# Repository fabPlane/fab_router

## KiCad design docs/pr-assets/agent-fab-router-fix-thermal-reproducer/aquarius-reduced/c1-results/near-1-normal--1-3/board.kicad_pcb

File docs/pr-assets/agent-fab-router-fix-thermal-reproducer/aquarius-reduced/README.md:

# Rotated back-layer thermal failure reduced from the completed baseline

This static native reproducer preserves Aquarius U1.39 (315-degree rounded
rectangle, 75 micrometre corner radius) and its B.Cu zone. It has one pad,
three 0.2032 mm tracks, no vias, and one zone. Its sole native error is
`starved_thermal`: one spoke, minimum two. This is not a router fix or a new
routing benchmark. All 27 baseline thermal errors remain unresolved.

Fresh native refill plus DRC, same host and cores 20–25, three repeats per row:

| Fixture control | Before: all tracks | After: indicated deletion |
| --- | ---: | ---: |
| First track removed | 1 error, 0 opens each | 0 errors, 0 opens each |
| Second track removed | 1 error, 0 opens each | 0 errors, 0 opens each |
| Third track removed | 1 error, 0 opens each | 0 errors, 0 opens each |
| All tracks removed | 1 error, 0 opens each | 0 errors, 0 opens each |

The shared before column describes the same three runs, not twelve runs.
Fifteen native checks total. Deleting obstacles is a diagnostic control and
would discard intended routing; it is not an acceptable production remedy.
The three non-ground tracks have different nets. Their terminals have been
removed, so zero opens in this static fixture does not establish completion
of those nets. There is no routing attempt, engine regression, or native
transaction implementation here.

The reducer first retained objects whose native bounding boxes intersect a
2 mm square radius around the pad, then deleted pad/copper/zone UUID groups
while requiring the exact target and no other error. Single-object deletion
trials finish the search. This establishes irreducibility only among retained
candidate objects; the board outline, zone polygon, graphics and unused net
definitions have not been geometrically minimized. `reduction.json` retains
24 trials and their exact native findings.

`provenance.json` verifies that pad geometry, each retained track and the full
zone definition (excluding refill polygons) match the completed baseline
output. Both project and rule sidecars match the output and original input
byte-for-byte. The pad position is the baseline output position, with its
previously recorded +8/-46 nm displacement from the original input. That
small displacement is not attributed to the failure. `LICENSE` preserves
the source board license.

`board.dsn` is a native export for further engine diagnostics. It does not
encode native thermal metadata and is not claimed to reproduce native
starvation when routed independently. Keep the native board and sidecars.
`results/` retains all fifteen refilled boards, native JSON reports and hashes.
The comparison image uses actual B.Cu exports after refill.

From the engine repository root, using native version 10.0.6:

```bash
asset=docs/pr-assets/agent-fab-router-fix-thermal-reproducer/aquarius-reduced
PYTHONDONTWRITEBYTECODE=1 taskset -c 20-25 nice -n 10 timeout 600 /usr/bin/python3 "$asset/verify.py" --out /tmp/aquarius-native-controls
source_run="$HOME/bench/repos/fab_pcb/benchmarks/autorouter/results/baseline-20261018/runs/run-20261018T135444.397318Z-062/fab-router/final.kicad_pcb"
PYTHONDONTWRITEBYTECODE=1 taskset -c 20-25 nice -n 10 timeout 1200 /usr/bin/python3 "$asset/reduce.py" --source "$source_run" --out /tmp/aquarius-reduction
PYTHONDONTWRITEBYTECODE=1 taskset -c 20-25 nice -n 10 timeout 120 /usr/bin/python3 "$asset/provenance.py" --source "$source_run" --original "$HOME/bench/repos/fab_pcb/benchmarks/autorouter/cases/kitspace-aquarius-j4/board.kicad_pcb" --out /tmp/aquarius-provenance
kicad-cli pcb export svg --layers B.Cu --page-size-mode 2 --exclude-drawing-sheet --mode-single --output /tmp/aquarius-all.svg /tmp/aquarius-native-controls/all-1/board.kicad_pcb
kicad-cli pcb export svg --layers B.Cu --page-size-mode 2 --exclude-drawing-sheet --mode-single --output /tmp/aquarius-control.svg /tmp/aquarius-native-controls/without-track-1-1/board.kicad_pcb
python3 "$asset/render.py" /tmp/aquarius-all.svg /tmp/aquarius-control.svg /tmp/aquarius-comparison.svg
rsvg-convert /tmp/aquarius-comparison.svg -o /tmp/aquarius-comparison.png
taskset -c 20-25 nice -n 10 timeout 900 bash -c 'bun run typecheck && bun run check:layers && bun run test'
```

Production source and engine tests remain unchanged. No frozen cases, checker,
scoring or shared runtime were edited. No full sweep or history row is added
because these are static native checks without a router run.

## Local-axis corridor audit

`local-corridors.py` reads the fifteen retained native outputs without routing
or refilling. It verifies their board/report hashes against `results/summary.json`
and measures positive-area polygon subtraction on B.Cu. Rectangles start at
local pad edges, rotate with the 315-degree pad, and extend 0.508 mm. These are
candidate geometric corridors, not resolved native thermal spokes. Rounded
corners and a strip wider than the pad make the stored-width test especially
unsuitable as a universal criterion.

All three repeats have identical areas for each configuration:

| Static native control | Native errors before → after | Fully covered 0.100 mm local corridors | Fully covered 0.508 mm local corridors |
| --- | --- | --- | --- |
| All tracks retained | 1 → 1 | −x | none |
| Track 1 removed | 1 → 0 | −x, −y | none |
| Track 2 removed | 1 → 0 | +x, −x | none |
| Track 3 removed | 1 → 0 | −x, +y | none |
| All tracks removed | 1 → 0 | +x, −x, +y, −y | none |

Before refers to the same previously measured all-track configuration;
this audit adds no native runs. The native checker accepts every deletion
control even though no full stored-width rectangle is covered. This rejects
that rectangle criterion as a general safety test. The narrow rectangles
explain which direction each obstacle blocks in this fixture, but their
agreement with the native findings is not a general spoke-count algorithm,
effective-rule resolution, connectivity proof, or routing remedy.

For every board, direction and width, controls require full self-coverage,
no empty-copper coverage, and partial coverage with a half-length strip.
A long-axis point hits the actual native pad under the chosen rotation;
the opposite rotation convention fails that control. Two independent audit
invocations produce byte-identical JSON. `local-results/` contains the
measurements and chart; the existing `results/` retains the source boards
and reports. Native imports emit existing library diagnostic messages, kept
in the raw log. Engine source/tests remain unchanged.

```bash
asset=docs/pr-assets/agent-fab-router-fix-thermal-reproducer/aquarius-reduced
PYTHONDONTWRITEBYTECODE=1 taskset -c 20-25 nice -n 10 timeout 120 /usr/bin/python3 "$asset/local-corridors.py" --out /tmp/aquarius-local-corridors
rsvg-convert /tmp/aquarius-local-corridors/comparison.svg -o /tmp/aquarius-local-corridors/comparison.png
```

## Complete-track translation diagnostic

Added a native translation sweep on the reduced rotated B.Cu fixture. Each trial retains the rounded pad, zone, project/rules and all three tracks, changing only both endpoints of one track by the same outward displacement. This compares relocation against the earlier deletion controls; it is not routing or connectivity preservation.

Same static fixture, machine, native version 10.0.6 and cores 20–25; three fresh refill/DRC checks per configuration. Entries are native errors in every repeat:

| Selected outward translation | Before: 0 µm | 25 µm | 50 µm | 100 µm | 200 µm | 400 µm |
| --- | ---: | ---: | ---: | ---: | ---: | ---: |
| Track 1, local −y | 1 | 1 | 1 | 1 | 1 | 1 |
| Track 2, local +x | 1 | 1 | 1 | 0 | 0 | 0 |
| Track 3, local +y | 1 | 1 | 1 | 0 | 0 | 0 |

The baseline column shares three checks across rows; 48 checks total. All retain one pad, three tracks, no vias and one zone. The 0.100 mm filled corridors recover +x for track 2 and +y for track 3 at every native-clean displacement. These rectangles are diagnostics, not a general spoke-count rule. The sweep brackets a change between 50 and 100 µm for tracks 2 and 3; it does not identify a minimum safe clearance. Moving track 1 by up to 400 µm is insufficient. Track endpoint changes would disconnect original routing, and the reduced fixture lacks those other-net terminals. Zero reported opens therefore does not establish completion. No general guard, production fix, frozen benchmark improvement or pin bump is claimed. The full baseline remains 39/78 passes, 13/26 cases passing 3/3, 120 opens and 27 unresolved native thermal errors.

Reproduce from the repository root, with a fresh output directory:

```bash
asset=docs/pr-assets/agent-fab-router-fix-thermal-reproducer/aquarius-reduced
PYTHONDONTWRITEBYTECODE=1 taskset -c 20-25 nice -n 10 timeout 900 /usr/bin/python3 "$asset/translate-tracks.py" --out /tmp/aquarius-translations
rsvg-convert /tmp/aquarius-translations/comparison.svg -o /tmp/aquarius-translations/comparison.png
taskset -c 20-25 nice -n 10 timeout 900 bash -c 'bun run typecheck && bun run check:layers && bun run test'
```

`translation-results/` retains all 48 boards/reports, exact input/output hashes, displacement vectors, local filled-corridor measurements and raw logs. Repeated native findings and corridor measurements are asserted identical. Engine source/tests are unchanged.

### Sequential full-board proposal replay

`compose-generated.py` applies the previously accepted R20 and U1.39 proposals
in sequence, validating each against the latest accepted native error report and
terminal partition. Rejection or checker failure preserves the latest accepted
bytes and baseline. Controls reject a deliberately stale-baseline mutation.
This is a static diagnostic using published witnesses, not a production repair.

| Full board, same machine, three repeats | Original | After R20 | After U1.39 |
| --- | ---: | ---: | ---: |
| Native errors per repeat | 6 | 5 | 4 |
| Opens per repeat | 15 | 15 | 15 |
| Terminals preserved | 234 | 234 | 234 |
| Terminal groups | 74 | 74 | 74 |

All three selected byte hashes agree. A fresh native refill of each selected
board reproduces its four errors and terminal partition. Each accepted error
multiset is a strict subset of its immediate predecessor; no connected terminal
pair is lost. Four thermal errors and fifteen opens remain unresolved. The
frozen router benchmark score has not changed or been rerun for this diagnostic.

```sh
asset=docs/pr-assets/agent-fab-router-fix-thermal-reproducer/aquarius-reduced
PYTHONDONTWRITEBYTECODE=1 /usr/bin/python3 "$asset/compose-generated.py" --controls
PYTHONDONTWRITEBYTECODE=1 taskset -c 20-25 nice -n 10 timeout 1800 /usr/bin/python3 "$asset/compose-generated.py" --out /tmp/composed-native
PYTHONDONTWRITEBYTECODE=1 taskset -c 20-25 nice -n 10 timeout 120 /usr/bin/python3 "$asset/verify-composed.py" --results "$asset/composed-generated-results"
/usr/bin/python3 "$asset/render-composed.py" /tmp/composed-native
```

`composed-generated-results/` retains compressed boards/native reports, exact
sidecars, byte hashes, terminal groups, controls, logs and the comparison image.
The independent verifier regenerates candidate geometry from published witness
metadata and checks all twelve reports and native terminal partitions.

### Bind retained native boards to each sequential proposal

The sequential verifier previously regenerated the proposed bytes and checked
native terminal partitions separately. A substituted checked board could keep
the same terminal partition and pass despite having different design geometry.
The verifier now compares every checked board's complete design tree against its
corresponding original, candidate or final replay input. It permits top-level
item ordering, numeric formatting and zone `filled_polygon` output changes.
Zone definitions, thermal settings, footprints, pads, copper and board setup
remain part of the comparison. Both native rule sidecars must match the source.

Five controls use the same retained three-repeat dataset on the same machine,
one verifier invocation per control before and after. Artifact manifest hashes
are rebound after substitution, so these exercise semantic checks rather than
only digest checks. The before revision is `8ee4122`.

| Diagnostic verifier control | Before | After |
| --- | --- | --- |
| Original twelve native board/report pairs | Accept | Accept |
| Substitute final candidate for baseline board | Accept (bug) | Reject |
| Substitute baseline for first candidate board | Accept (bug) | Reject |
| Substitute baseline for final replay board | Accept (bug) | Reject |
| Replace candidate native rule file | Accept (bug) | Reject |

The accepted full-board diagnostic still has 6 → 5 → 4 errors and fifteen opens
in each of three repeats. This checks retained evidence; it does not rerun native
DRC or authenticate externally supplied reports. The production failure remains
unfixed. No routing benchmark was rerun and no score or speed gain is claimed.
The completed shared baseline was inspected read-only: it confirms 39/78 passes,
13/26 valid cases, 120 opens and 27 new `starved_thermal` errors.

```sh
asset=docs/pr-assets/agent-fab-router-fix-thermal-reproducer/aquarius-reduced
PYTHONDONTWRITEBYTECODE=1 taskset -c 20-25 nice -n 10 timeout 600 /usr/bin/python3 "$asset/composed-binding-controls.py" --out /tmp/composed-binding-controls
/usr/bin/python3 "$asset/render-binding.py" "$asset/binding-results"
taskset -c 20-25 nice -n 10 timeout 900 bash -c 'bun run typecheck && bun run check:layers && bun run test'
```

`binding-results/` retains before/after control summaries, raw logs, validation
output and the measured chart. These are static verifier controls, not router
benchmark runs.

### Remaining composed-board thermal failures

The latest experiment starts from the previously composed full board (six native errors reduced to four), and searches the two nearest foreign straight tracks around each remaining thermal pad. Each track receives ten signed normal translations with endpoint links. Candidates are accepted only if native errors strictly decrease, the positive-net terminal inventory remains exact, no connected terminal pair is lost, and opens do not increase. Every rejection returns the exact starting board bytes.

Same board, rule sidecars, machine `hyper-ms-lin`, cores 20–25, native version 10.0.6; three repeats:

| Remaining pad | Proposals per repeat | Target remains | Accepted repeats | Errors before / selected | Opens before / selected |
| --- | ---: | ---: | ---: | ---: | ---: |
| C1.2 | 20 | 20/20 | 0/3 | 4 / 4 | 15 / 15 |
| U1.53 | 20 | 13/20 | 0/3 | 4 / 4 | 15 / 15 |
| U1.46 | 20 | 20/20 | 0/3 | 4 / 4 | 15 / 15 |
| U1.48 | 20 | 20/20 | 0/3 | 4 / 4 | 15 / 15 |

U1.53 loses its thermal error in seven proposals per repeat, but six introduce shorts and one clearance errors; all seven also add solder-mask bridge errors. Two U1.46 proposals and one U1.48 proposal lose connected terminal pairs. All 243 native checks are retained.

These are static native diagnostics, not router benchmark runs. The full frozen reference remains **39/78 passing runs, 13/26 valid cases, 120 opens and 27 new thermal errors**. No routing score or speed gain is claimed. No engine, adapter, frozen input, checker or scoring code changed.

Independent replay verifies native reports, rebuilt terminal partitions, target coverage, proposal ranking/geometry, selected bytes and manifests. The new audit compares every checked design and both native rule sidecars to its proposed input. Nine rejected boards (three proposals, repeated three times) show native net reassignment after save; exact differences are retained. Baselines match their proposed designs. No candidate is accepted. Identical compressed artifacts use relative symlinks within the evidence directory. Its rejection table distinguishes target removal from added clearance errors, shorts and connectivity loss.

Required checks: typecheck PASS; layer checks 65 files / zero violations; 859 tests / zero failures / 398454 assertions.

Reproduce from repository root:

```sh
asset=docs/pr-assets/agent-fab-router-fix-thermal-reproducer/aquarius-reduced
results=$asset/remaining-composed-results
mkdir -p /tmp/remaining-source
gzip -dc "$results/source.kicad_pcb.gz" > /tmp/remaining-source/source.kicad_pcb
cp "$results/source.kicad_pro" "$results/source.kicad_dru" /tmp/remaining-source/
PYTHONDONTWRITEBYTECODE=1 taskset -c 20-25 nice -n 10 timeout 2400 /usr/bin/python3 "$asset/generated-transaction.py" --all-targets --track-limit 2 --source /tmp/remaining-source/source.kicad_pcb --out /tmp/remaining-native
PYTHONDONTWRITEBYTECODE=1 taskset -c 20-25 nice -n 10 timeout 900 /usr/bin/python3 "$asset/audit-remaining.py" --results /tmp/remaining-native --source /tmp/remaining-source/source.kicad_pcb
PYTHONDONTWRITEBYTECODE=1 taskset -c 20-25 nice -n 10 timeout 900 /usr/bin/python3 "$asset/audit-remaining.py" --results "$results" --source /tmp/remaining-source/source.kicad_pcb
/usr/bin/python3 "$asset/render-remaining.py" "$results"
taskset -c 20-25 nice -n 10 timeout 900 bash -c 'bun run typecheck && bun run check:layers && bun run test'
```

Earlier minimized boards, composed native repair evidence, exact reproduction commands and images remain in the [diagnostic README](https://github.com/fabPlane/fab_router/blob/agent/fab-router-fix-thermal-reproducer/docs/pr-assets/agent-fab-router-fix-thermal-reproducer/aquarius-reduced/README.md). Native transaction ownership and production integration remain open work.

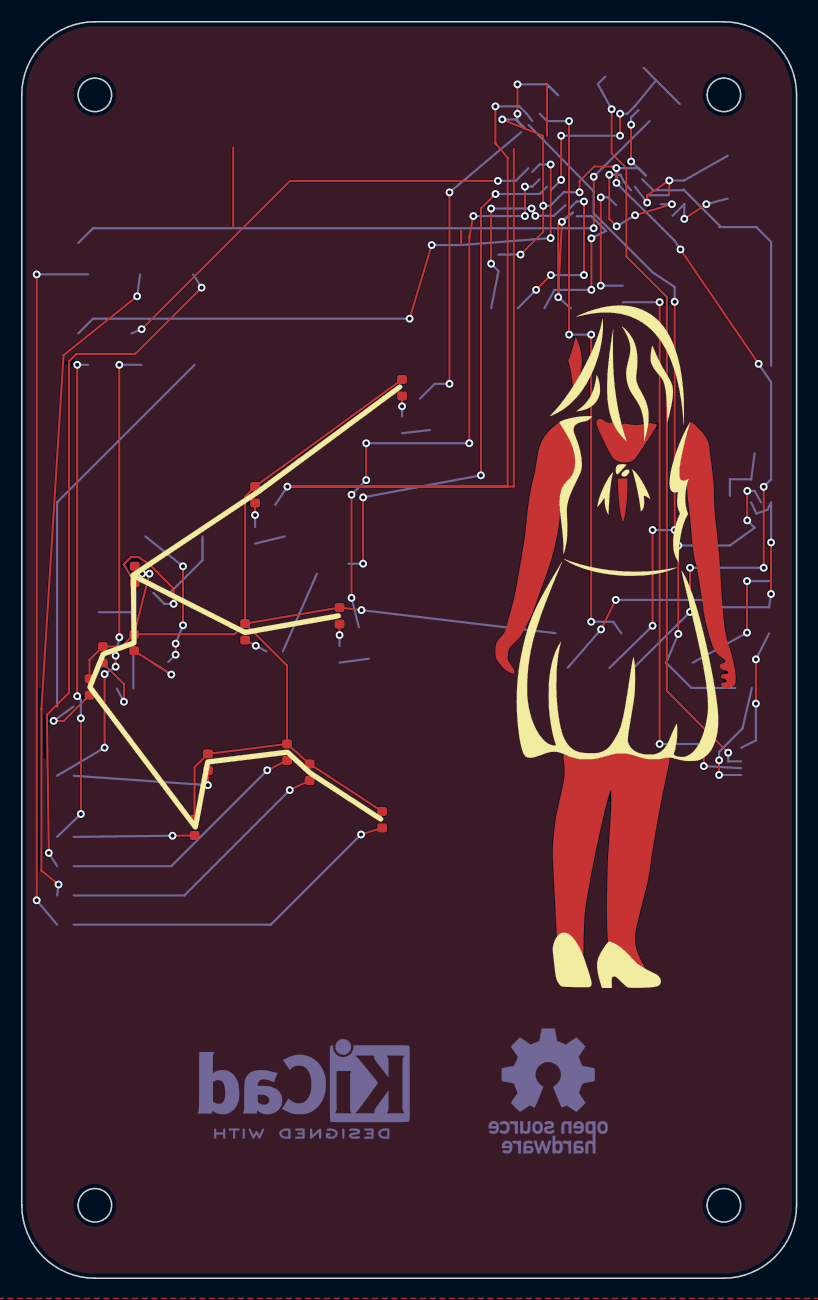
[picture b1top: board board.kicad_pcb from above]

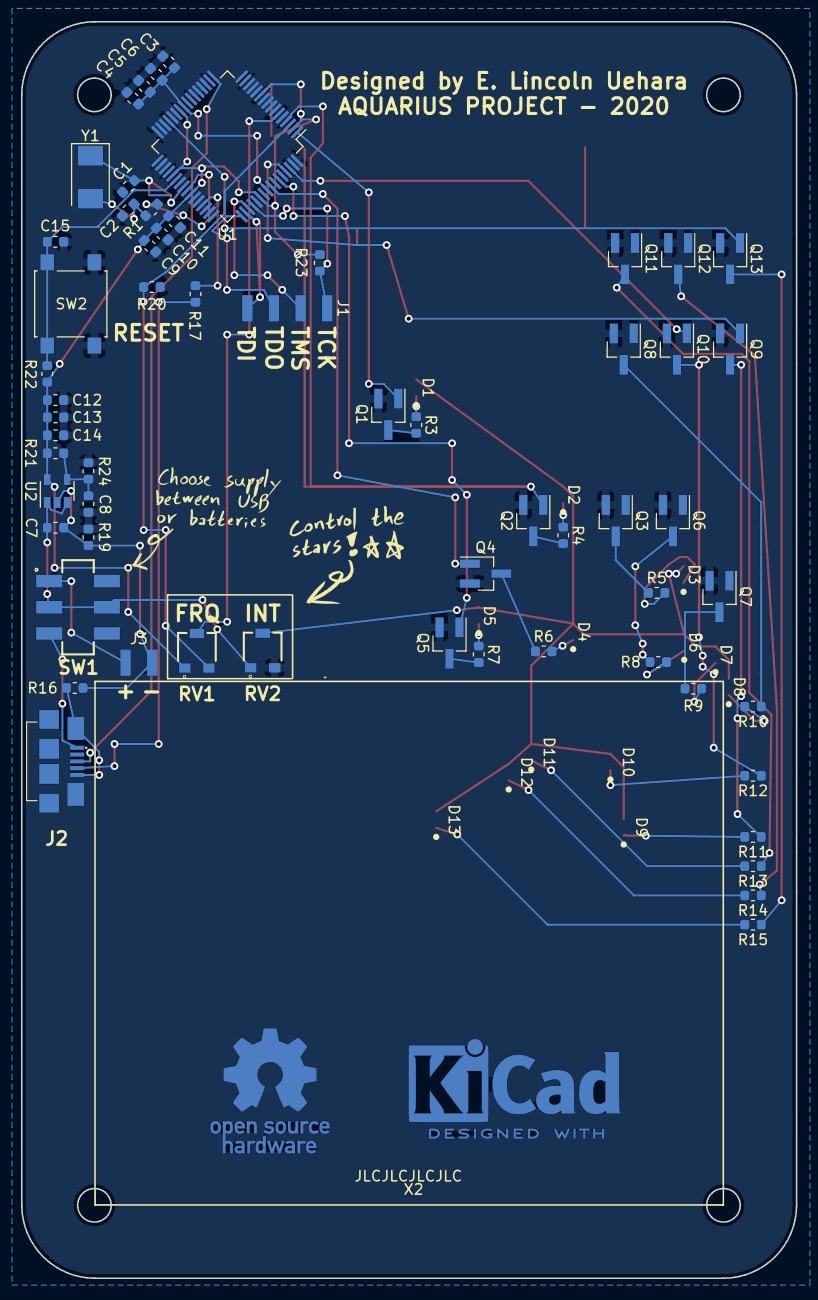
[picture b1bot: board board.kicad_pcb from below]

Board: 2 copper layers, 74.0 x 120.0 mm, 79 parts (64 on the bottom side), 63 nets.

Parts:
C1, C2: 10pF; C_0603_1608Metric
C3: 2.2uF; C_0603_1608Metric
C4, C7, C14: 1.0uF; C_0603_1608Metric
C5, C6, C10, C12, C15: 0.1uF; C_0603_1608Metric
C8, C9, C11, C13: 0.01uF; C_0603_1608Metric
D1, D2, D3, D4, D5, D6, D7, D8, D9, D10, D11, D12, D13: LED; LED_STAR_0603
J1: Conn_01x04; PinHeader_1x04_P2.54mm_SMD
J2: USB_B_Micro; ZX62B5PA33
J3: Conn_01x02; PinHeader_1x02_P2.54mm_SMD
Q1, Q2, Q3, Q4, Q5, Q6, Q7, Q8, Q9, Q10, Q11, Q12, Q13: DTC114E; SOT-23_Handsoldering
R1, R16, R17, R19, R20: 0; R_0603_1608Metric
R3, R4, R5, R6, R7, R8, R9, R10, R11, R12, R13, R14, R15: R100; R_0603_1608Metric
R21: 51k; R_0603_1608Metric
R22: 10k; R_0603_1608Metric
R23: 100k; R_0603_1608Metric
R24: 30k; R_0603_1608Metric
RV1, RV2: R_POT; PVG3A
SW1: SW_DPDT_x2; JS202011SCQN
SW2: SW_Push; SW_SPST_B3S-1000
U1: TM4C1231C3PM; LQFP-64_10x10mm_P0.5mm
U2: TPS73633DBV; SOT-23-5
X1: theGirl
X2: jlcpcb_order
X3: DesignedWithKicad; KiCad-Logo2_8mm_Copper
X4: OpenSourceHardware; OSHW-Logo_11.4x12mm_Copper
X5: choose_indication
X6: control_indication
Y1: 16MHz; Crystal_SMD_Abracon_ABM3-2Pin_5.0x3.2mm

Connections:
+3V3: C9.1, C10.1, C11.1, C12.1, C13.1, C14.1, R21.1, R22.1, R23.2, RV1.1, U1.2, U1.11, U1.26, U1.37, U1.42, U1.54, U2.5
/Inputs/D+: J2.3, U1.17
/Inputs/D-: J2.2, U1.18
/Inputs/LED_PWR: D1.2, D2.2, D3.2, D4.2, D5.2, D6.2, D7.2, D8.2, D9.2, D10.2, D11.2, D12.2, D13.2, RV2.2
/Inputs/PB0: R17.2, U1.45
/Inputs/POT00: RV1.2, U1.6
/Inputs/RST: C15.1, R22.2, SW2.2, U1.38
/Inputs/TCK: J1.1, R23.1, U1.52
/Inputs/TDI: J1.4, U1.50
/Inputs/TDO: J1.3, U1.49
/Inputs/TMS: J1.2, U1.51
/Inputs/USB_PWR: J2.1, SW1.3
/Leds/Stars/LED0: Q1.1, U1.1
/Leds/Stars/LED1: Q2.1, U1.4
/Leds/Stars/LED2: Q3.1, U1.58
/Leds/Stars/LED3: Q4.1, U1.57
/Leds/Stars/LED4: Q5.1, U1.59
/Leds/Stars/LED5: Q6.1, U1.60
/Leds/Stars/LED6: Q7.1, U1.16
/Leds/Stars/LED7: Q8.1, U1.15
/Leds/Stars/LED8: Q9.1, U1.61
/Leds/Stars/LED9: Q10.1, U1.62
/Leds/Stars/LED10: Q11.1, U1.23
/Leds/Stars/LED11: Q12.1, U1.24
/Leds/Stars/LED12: Q13.1, U1.29
GNDA: R20.2, RV1.3, U1.3
GNDD: C1.2, C2.2, C3.2, C4.2, C5.2, C6.2, C8.2, C9.2, C10.2, C11.2, C12.2, C13.2, C14.2, C15.2, Q1.2, Q2.2, Q3.2, Q4.2, Q5.2, Q6.2, Q7.2, Q8.2, Q9.2, Q10.2, Q11.2, Q12.2, Q13.2, R19.2, R20.1, R24.2, RV2.3, SW2.1, U1.5, U1.7, U1.8, U1.9, U1.10, U1.12, U1.13, U1.14, U1.19, U1.20, U1.21, U1.22, U1.27, U1.28, U1.30, U1.31, U1.32, U1.34, U1.35, U1.39, U1.43, U1.44, U1.46, U1.47, U1.48, U1.53, U1.55, U1.63, U1.64
GNDPWR: C7.2, J3.2, R16.2, R19.1, U2.2
unnamed: C1.1, U1.40, Y1.1
unnamed: C2.1, R1.2, Y1.2
unnamed: C3.1, C4.1, C5.1, C6.1, U1.25, U1.56
unnamed: C8.1, R21.2, R24.1, U2.4
unnamed: D1.1, R3.2
unnamed: D2.1, R4.2
unnamed: D3.1, R5.2
unnamed: D4.1, R6.2
unnamed: D5.1, R7.2
unnamed: D6.1, R8.2
unnamed: D7.1, R9.2
unnamed: D8.1, R10.2
unnamed: D9.1, R11.2
unnamed: D10.1, R12.2
unnamed: D11.1, R13.2
unnamed: D12.1, R14.2
unnamed: D13.1, R15.2
unnamed: J2.4, R17.1
unnamed: J2.5, J2.6, R16.1
unnamed: J3.1, SW1.1
unnamed: Q1.3, R3.1
unnamed: Q2.3, R4.1
unnamed: Q3.3, R5.1
unnamed: Q4.3, R6.1
unnamed: Q5.3, R7.1
unnamed: Q6.3, R8.1
unnamed: Q7.3, R9.1
unnamed: Q8.3, R10.1
unnamed: Q9.3, R11.1
unnamed: Q10.3, R12.1
unnamed: Q11.3, R13.1
unnamed: Q12.3, R14.1
unnamed: Q13.3, R15.1
unnamed: R1.1, U1.41
VBUS: C7.1, RV2.1, SW1.2, SW1.5, U2.1, U2.3

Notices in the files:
docs/pr-assets/agent-fab-router-fix-thermal-reproducer/aquarius-reduced/c1-results/near-1-normal--1-3/board.kicad_pcb:
creativecommons.org/licenses/by/4.0
License: CC BY 4.0
